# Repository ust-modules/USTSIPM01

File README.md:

# USTSIPM01 — Silicon photomultiplier (SiPM) interface module  

Complete analog front‑end for Silicon Photomultipliers (SiPM). The module provides resistor-configurable high‑voltage bias for the SiPM sensor and a low‑noise, wideband readout stage suitable for timing and amplitude measurements.

## Features

* Footprint for onsemi **MicroFC‑60035‑SMT** SiPM (6×6 mm, 35 µm microcells).
* On‑board high‑voltage boost converter MAX5026 generating the SiPM bias from the +5 V rail.
* Precision feedback network with design equation Vout = 1.25 V × (1 + R2/R3); default configuration targets to 31.7 V bias.
* Low‑noise **wideband amplifier** stage OPA836 for SiPM signal readout.
* Pin-header connector for lab bring‑up and diagnostics.

## Block Diagram

```mermaid
flowchart LR
    V["3V6"] -->|Bias supply| MAX5026["MAX5026 Boost"]
    MAX5026 -->|VBIAS 25-32 V| SiPM["SiPM MicroFC-60035"]
    SiPM -->|A| OPA836["OPA836 Readout"]
    OPA836 --> OUT["OUT"]
    V33["+3.3 V"] --> OPA836
```

## Electrical Characteristics (module)

* Supply rails: +3.6 V (bias converter), +3.3 V (analog stage).
* SiPM bias range: designable in \~25–32 V via resistor ratio (see below). Default assembly ≈ 31.7 V.
* Output: single‑ended, wideband path suitable for 50 Ω instrumentation (use external 50 Ω termination at scope/DAQ as required).

> Note (SiPM operating point): The sensor is biased at Vout = VBR + VOV, where VBR is the device’s breakdown voltage and VOV is the selected overvoltage. Typical recommended VOV = 1…5 V. Temperature coefficient of VBR ≈ +21.5 mV/°C (adjust bias accordingly).

## Bias Network Design

The MAX5026 feedback follows:

```
Vout = 1.25 V × (1 + R2/R3)
```

**Default population** (R2 = 3.9 MΩ, R3 = 160 kΩ) yields:

```
Vout ≈ 1.25 × (1 + 3.9M/160k) ≈ 31.7 V
```

**Example design** for MicroFC‑60035 with typical VBR ≈ 24.7 V:

* For **VOV = 3.0 V** → target **Vout ≈ 27.7 V**.
* Choose standard values to satisfy 1.25 × (1 + R2/R3) ≈ 27.7. For example, **R3 = 160 kΩ**, **R2 ≈ 3.394 MΩ** (use 3.40 MΩ or parallel combination). Verify with measurement on the assembled board.

> Keep the feedback resistors in the **MΩ** range to minimize divider current, and place them tight to the FB node. Use a low‑leakage layout around FB.
> Treat the SiPM and the module as **ESD‑sensitive**.

## Operating Guidance

* Start at low overvoltage (e.g., +1…2 V above the measured VBR) and increase gradually while monitoring dark count and pulse shape.
* Observe the maximum average current rating of the chosen sensor (for 6×6 mm devices typically tens of mA). Avoid saturating the device with continuous high optical flux.

## Changeable Parameters

* **SiPM bias (R2/R3):** select to set the required overvoltage window for the specific sensor lot and operating temperature.
* **OPA836 gain (R10/R12):** non‑inverting stage; A\_v = 1 + R10/R12. Default R10 = 12 kΩ, R12 = 1 kΩ → A\_v ≈ 13 V/V (\~22.3 dB). Adjust these resistors to set the desired voltage gain. (See schematic).

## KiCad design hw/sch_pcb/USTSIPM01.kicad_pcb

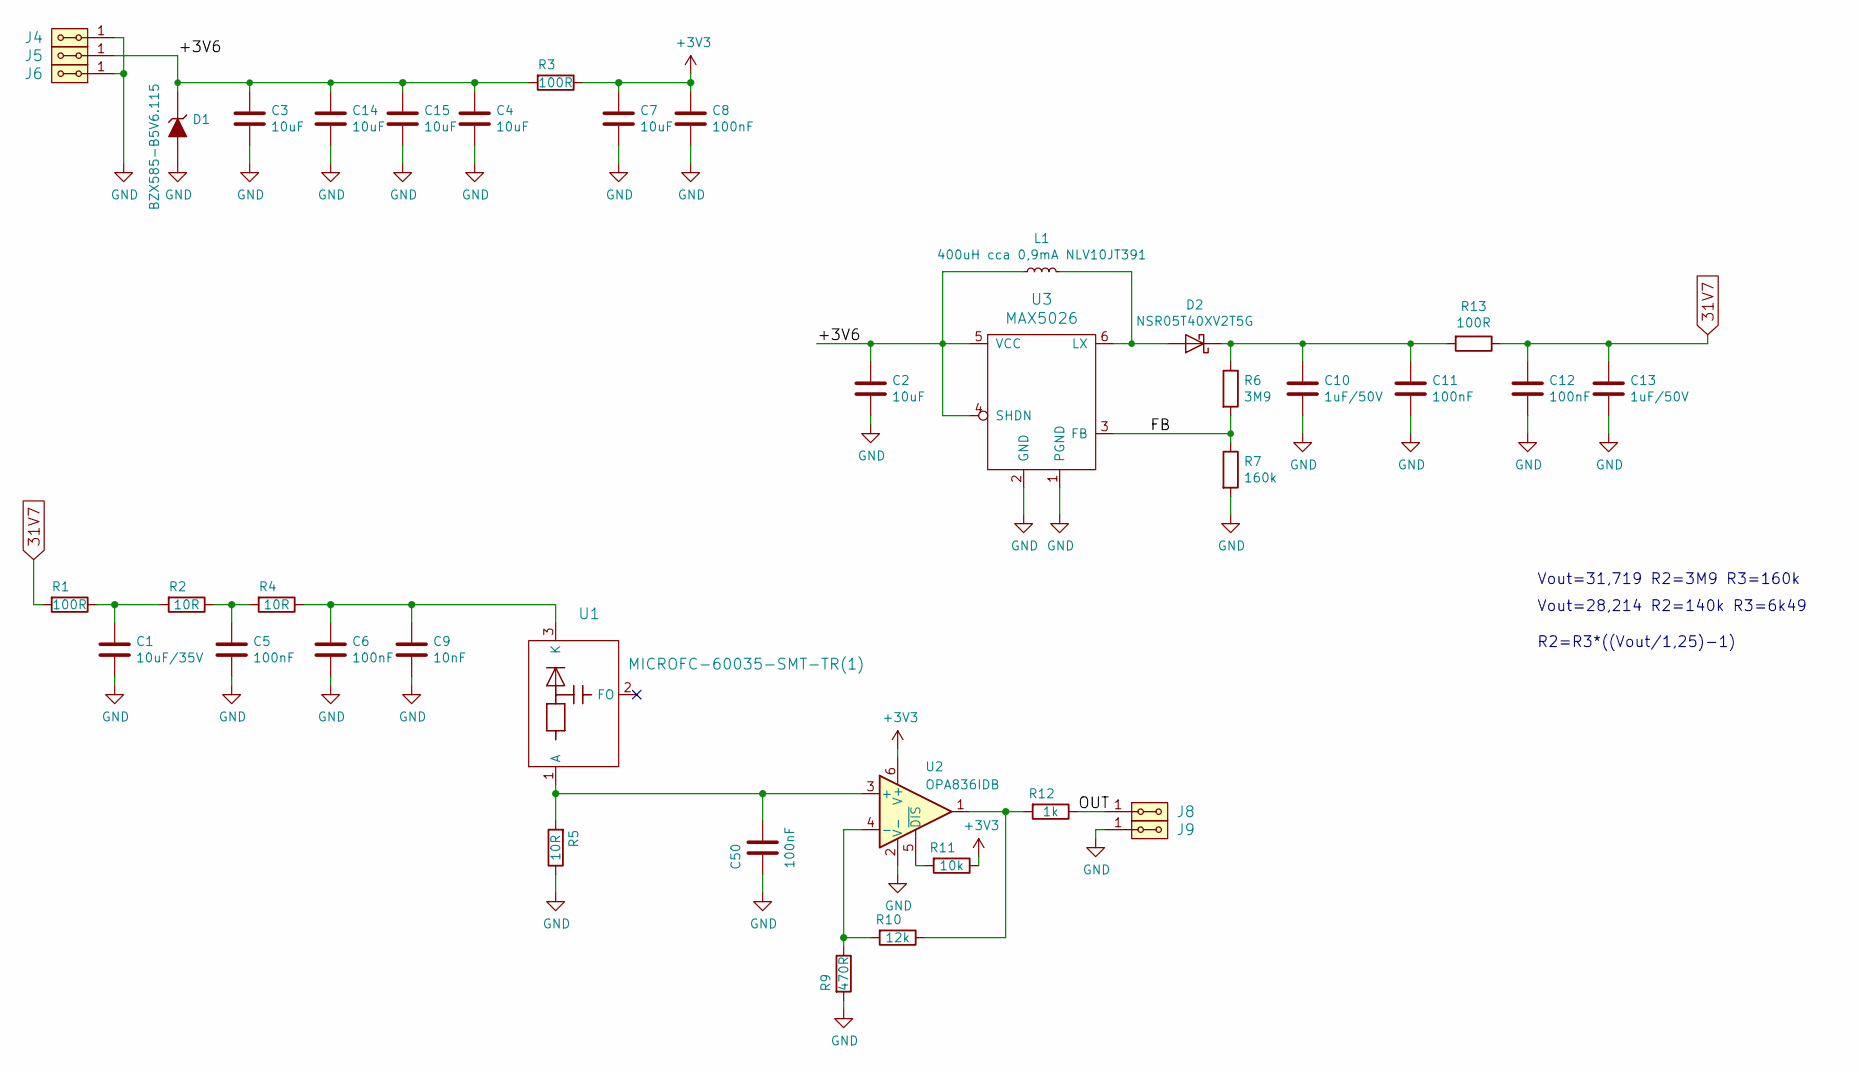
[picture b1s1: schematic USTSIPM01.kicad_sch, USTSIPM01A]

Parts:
C1: 10uF/35V; C_0805_2012Metric
C2, C3, C4, C7, C14, C15: 10uF; C_0805_2012Metric
C5, C6, C8, C11, C12, C50: 100nF; C_0805_2012Metric
C9: 10nF; C_0805_2012Metric
C10, C13: 1uF/50V; C_0805_2012Metric
D1: BZX585-B5V6.115; D_SOD-523
D2: NSR05T40XV2T5G; D_SOD-523
J4, J5, J6, J8, J9: HEADER_2x01_PARALLEL; Straight_2x01
L1: 400uH cca 0,9mA NLV10JT391; L_1210_3225Metric_Pad1.42x2.65mm_HandSolder
R1, R3, R13: 100R; R_0805_2012Metric
R2, R4, R5: 10R; R_0805_2012Metric
R6: 3M9; R_0805_2012Metric
R7: 160k; R_0805_2012Metric
R9: 470R; R_0805_2012Metric
R10: 12k; R_0805_2012Metric
R11: 10k; R_0805_2012Metric
R12: 1k; R_0805_2012Metric
U1: MICROFC-60035-SMT-TR(1); MicroFC−60035−SMT
U2: OPA836IDB; SOT-23-6
U3: MAX5026; SOT-23-6_Handsoldering

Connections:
31V7: C12.1, C13.1, R1.2, R13.1
+3V3: C7.1, C8.1, R3.1, R11.1, U2.6 (V+)
/+3V6: C2.1, C3.1, C4.1, C14.1, C15.1, D1.1 (K), J5.1, J5.2, L1.1, R3.2, U3.4 (SHDN), U3.5 (VCC)
/FB: R6.2, R7.1, U3.3 (FB)
/OUT: J8.1, J8.2, R12.1
GND: C1.2, C2.2, C3.2, C4.2, C5.2, C6.2, C7.2, C8.2, C9.2, C10.2, C11.2, C12.2, C13.2, C14.2, C15.2, C50.2, D1.2 (A), J4.1, J4.2, J6.1, J6.2, J9.1, J9.2, R5.1, R7.2, R9.2, U2.2 (V-), U3.1 (PGND), U3.2 (GND)
unnamed: C1.1, R1.1, R2.2
unnamed: C5.1, R2.1, R4.2
unnamed: D2.2 (A), L1.2, U3.6 (LX)
unnamed: C10.1, C11.1, D2.1 (K), R6.1, R13.2
unnamed: R10.1, R12.2, U2.1
unnamed: C50.1, R5.2, U1.1 (A), U2.3 (+)
unnamed: C6.1, C9.1, R4.1, U1.3 (K)
unnamed: R9.1, R10.2, U2.4 (-)
unnamed: R11.2, U2.5 (~DIS)

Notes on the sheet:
Vout=28,214 R2=140k R3=6k49
R2=R3*((Vout/1,25)-1)
Vout=31,719 R2=3M9 R3=160k

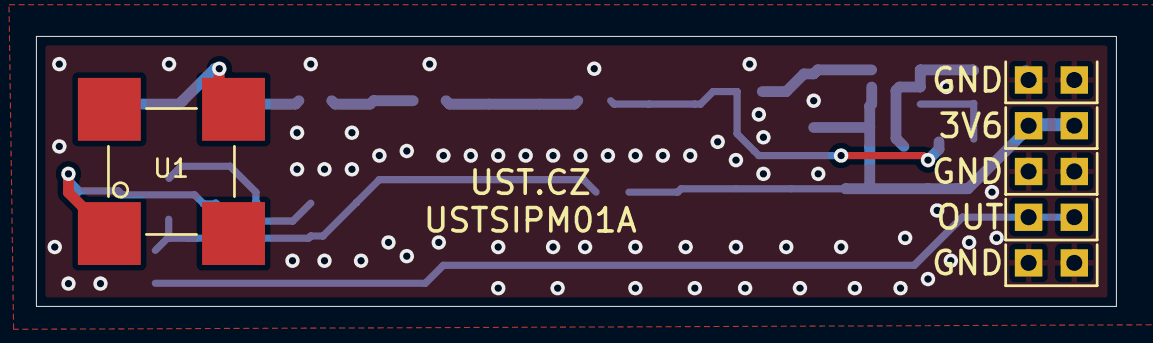
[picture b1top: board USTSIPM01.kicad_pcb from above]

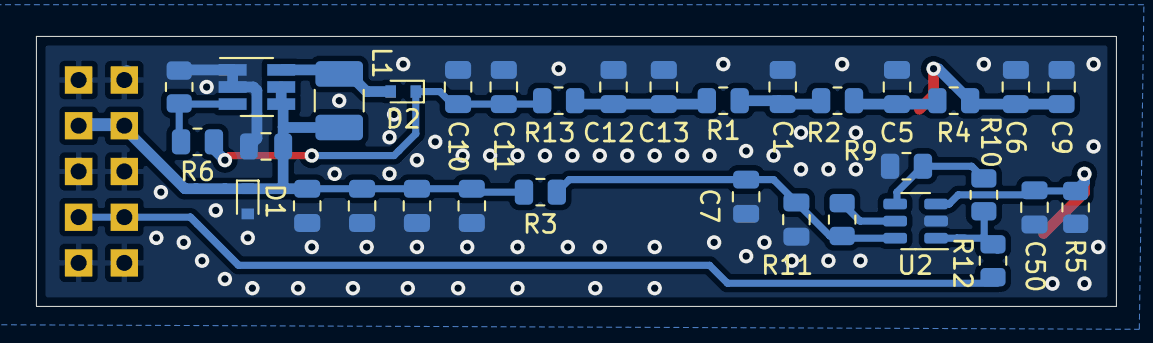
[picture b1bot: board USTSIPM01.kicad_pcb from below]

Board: 2 copper layers, 60.0 x 15.0 mm, 39 parts (33 on the bottom side), 15 nets.

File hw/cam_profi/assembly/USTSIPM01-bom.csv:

Component,Description,Part,References,Value,Footprint,Quantity Per PCB,Datasheet,ust_id
1,Unpolarized capacitor,C,C9,10nF,C_0805_2012Metric,1,~,5c70984712875079b91f8b49
2,,C-Device,C11C12,100nF,C_0805_2012Metric,2,,5c70984712875079b91f8b4c
3,Unpolarized capacitor,C,C5C6C8C50,100nF,C_0805_2012Metric,4,~,5c70984712875079b91f8b4c
4,Unpolarized capacitor,C,C3C4C7C14C15,10uF,C_0805_2012Metric,5,~,5c70984712875079b91f8b53
5,,C-Device,C2,10uF,C_0805_2012Metric,1,,5c70984712875079b91f8b53
6,Unpolarized capacitor,C,C1,10uF/35V,C_0805_2012Metric,1,~,628d183cdc56076e9a223682
7,,C-Device,C10C13,1uF/50V,C_0805_2012Metric,2,,5c70984712875079b91f8b6f
8,,D_ZENER,D1,BZX585-B5V6.115,D_SOD-523,1,,60879d38128750769ee58e48
9,,D_Schottky-Device,D2,NSR05T40XV2T5G,D_SOD-523,1,https://www.onsemi.com/pdf/datasheet/nsr05t40xv2-d.pdf,5c70984712875079b91f8b7b
10,"2x01 2.54 mm pitch header, 2 pins next to each other are connected",HEADER_2x01_PARALLEL,J4J5J6J8J9,HEADER_2x01_PARALLEL,Straight_2x01,5,,
11,,L_Small-Device,L1,"400uH cca 0,9mA NLV10JT391",L_1210_3225Metric_Pad1.42x2.65mm_HandSolder,1,,628d18f5dc56076e9a2236a9
12,Resistor,R,R2R4R5,10R,R_0805_2012Metric,3,~,5c70984512875079b91f896d
13,Resistor,R,R1R3,100R,R_0805_2012Metric,2,~,5c70984512875079b91f8977
14,,R-Device,R13,100R,R_0805_2012Metric,1,,5c70984512875079b91f8977
15,Resistor,R,R9,470R,R_0805_2012Metric,1,~,5c70984512875079b91f8986
16,Resistor,R,R12,1k,R_0805_2012Metric,1,~,5c70984512875079b91f898c
17,Resistor,R,R11,10k,R_0805_2012Metric,1,~,5c70984612875079b91f899f
18,Resistor,R,R10,12k,R_0805_2012Metric,1,~,5c70984612875079b91f89a1
19,,R-Device,R7,160k,R_0805_2012Metric,1,,628d19e8dc56076e9a2236eb
20,,R-Device,R6,3M9,R_0805_2012Metric,1,,62c7d4f48c8e243169d1938e
21,,MAX5026-MLAB_IO,U3,MAX5026,SOT-23-6_Handsoldering,1,https://datasheets.maximintegrated.com/en/ds/MAX5025-MAX5028.pdf,5c70984712875079b91f8b7c
22,,MICROFC-60035-SMT-TR(1),U1,MICROFC-60035-SMT-TR(1),MicroFC−60035−SMT,1,https://www.onsemi.com/pdf/datasheet/microc-series-d.pdf,60f907411287500165a96c1e
23,"Single Low-Power, 3.9GHz, Wideband, Ultra-Low Noise, Voltage-Feedback Operational Amplifier with Disable, SOT-23-6",OPA847xDBV,U2,OPA836IDB,SOT-23-6,1,https://www.ti.com/lit/ds/symlink/opa836.pdf,5c7273171287500b4e112ff8

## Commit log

2022-05-05 Edit schema
2022-05-05 Add submodule
2022-05-05 Update actions products
2022-05-16 Editing schema and PCB
2022-05-17 Editing PCB
2022-05-21 Edit PCB
2022-05-24 Priprava vyrobnich dat
2022-05-24 Edit submodule
2022-05-24 Edit assets
2022-07-08 Edit UST ID for 3M9
2022-07-08 Edit
2022-07-08 aktualizace submodulu
2022-08-04 Update title block fields.
2023-09-09 Add a link to datasheet.
2025-09-21 Update project to KiCAD9
2025-09-21 Align schematics symbols to grid. Update PCB from schematic. Improve silkscreen. Move PCB to center of the page.
2025-09-21 Update README.md
    Fix image paths.
2025-09-21 Update readme. Explain module function.
2025-09-21 Update README.md
    Repair mermaid diagram.
2025-09-22 Update workflow files
